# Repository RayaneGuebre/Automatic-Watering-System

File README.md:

<h1 align="center">Automatic Watering System</h1>
<h3 align="center">An electronic system that automatically waters your plants every 12 hours</h3>
<p align="center">

</p>

## How it works
Each time the ESP32 wakes up from deep sleep, it sends a signal to the gate pin of the MOSFET. This allows current from the water pump to flow to the ground pin of the power source, activating the pump and delivering water to the thirsty plants. The ESP32 also reads the value from the potentiometer to regulate how much water flows through the tube, making it easy to adjust for a larger or smaller number of plants.
## Storytime
Last month, while walking, i noticed a wall that would have been beautiful with some climbing plants, and there were some, but the only problem was that almost all the plants seemed completely dry. and while thinking about that wall i had the idea for this project, after a month of designing and exams i finally finished it, 

## BOM

[Link Excel](https://diccollegeliege-my.sharepoint.com/:x:/g/personal/guebnadi_dic-college_be/EUuX6dw9avlKky0aWlI7B-UB21Nbo-P0he4uefEX8ywWqg?e=9ALEz9)

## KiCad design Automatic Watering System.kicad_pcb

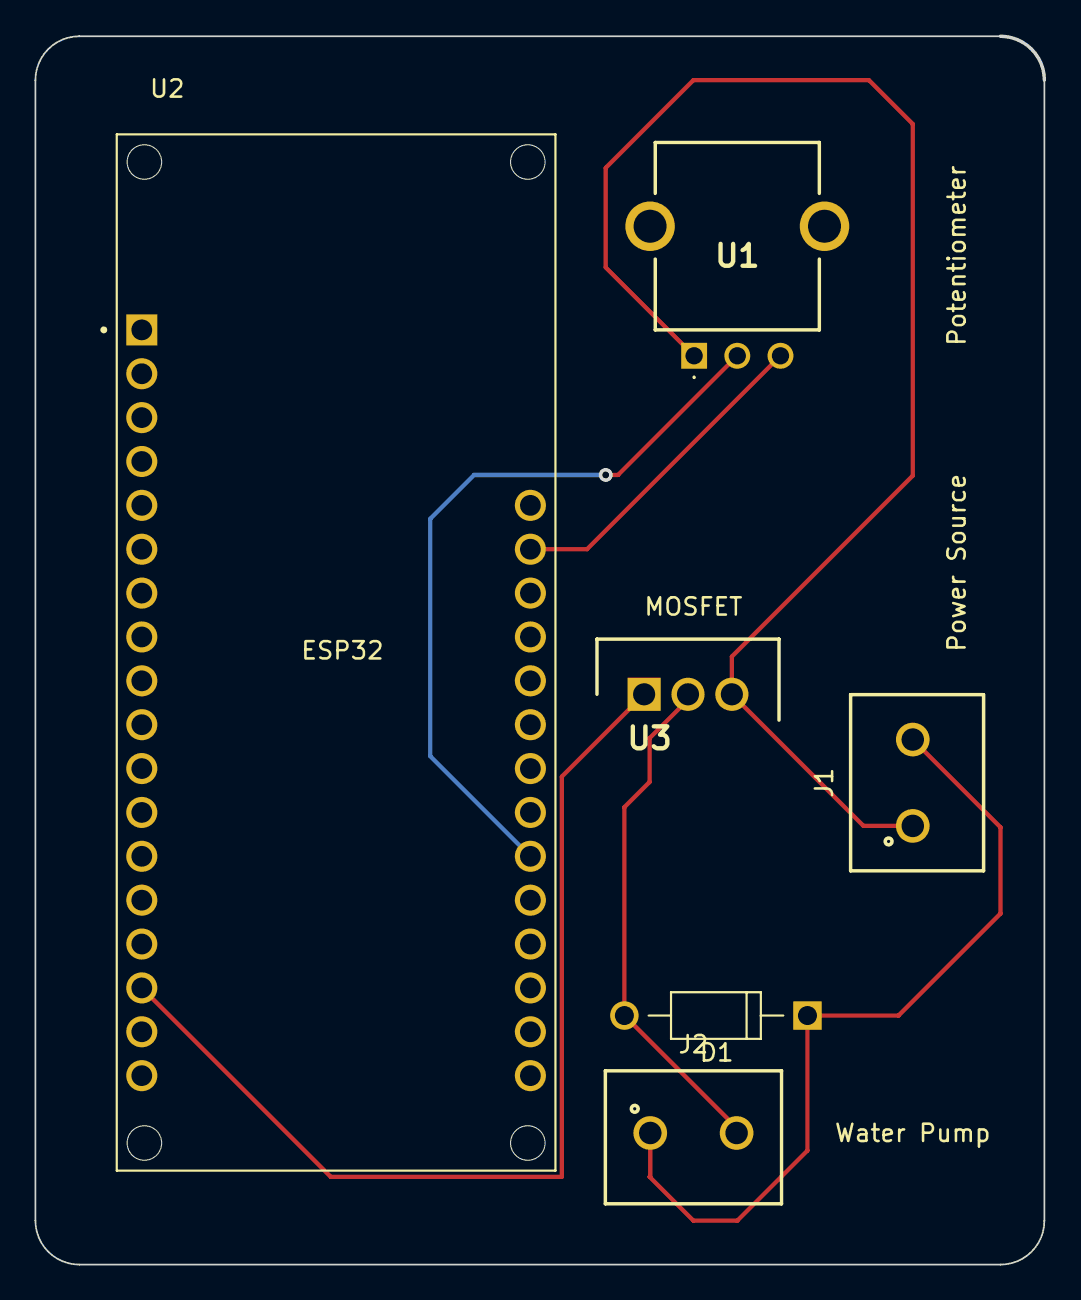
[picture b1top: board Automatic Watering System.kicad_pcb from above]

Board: 2 copper layers, 58.4 x 71.1 mm, 6 parts (0 on the bottom side), 6 nets.

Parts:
D1: 1N4007; DIOAD1060W80L520D270
J1, J2: 691137710002
U1: PTN091-V10115K1B; PTN091V10115K1B
U2: DFR0654; MODULE_DFR0654
U3: IRLZ44NPBF; TO254P469X1042X1967-3P

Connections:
unnamed: D1.A, J2.2, U3.2 (D)
unnamed: D1.C, J1.2, J2.1
unnamed: J1.1, U1.1 (CCW), U3.3 (S)
unnamed: U1.2 (WIPER), U2.24 (A1)
unnamed: U1.3 (CW), U2.2 (3.3V), U2.31 (3.3V)
unnamed: U2.16 (D2), U3.1 (G)

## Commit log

2025-05-29 Rename image(2).png to schematic.png
2025-05-31 Rename image(3).png to schematic.png
2025-06-07 code added
2025-06-07 journal updated
2025-07-11 I NEED TO LEARN TO SAVE STUFF BEFORE DELETING IT
2025-07-21 Fixing some issues with schematics and changing potentiometer
2025-07-21 Adding pcb image
2025-07-21 minor changes
2025-07-21 Adding BOM CSV
2025-07-23 Updating BOM
2025-07-23 Update and rename BOM watering system(Sheet1) (2).csv to BOM
2025-07-23 fixing some issues with the pcb
2025-07-27 addinc PCB step
2025-07-28 Added printable case
2025-07-28 Rename Case (1).stl to Case .stl
2025-07-31 opsie
2025-08-05 Adding diagram

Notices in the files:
README.md:
License: CC BY-NC 4.0
